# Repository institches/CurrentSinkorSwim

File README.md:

# CurrentSinkorSwim
Building a Current Sink for battery testing - Contextual Electronics

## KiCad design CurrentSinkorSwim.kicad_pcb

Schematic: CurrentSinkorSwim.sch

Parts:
J101, J103: Conn_01x02; Terminal_Block_200_thou
J102: Conn_01x03; Pin_Header_Straight_1x03_Pitch2.54mm

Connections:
/Current Control/Current_Sink+: J102.3, J103.1; also elsewhere on the board
/Power Regulation/Vin: J102.2; also elsewhere on the board
GND: J101.1, J103.2; also elsewhere on the board
unnamed: J101.2, J102.1

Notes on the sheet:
Battery Pack
Current Sink Input

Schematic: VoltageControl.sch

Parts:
C201: C; C_0805_HandSoldering
D201: D; D_SOD-523; MPN 1N4148WT-7
R201: 28.7K; R_0805
R202: 9K; R_0805
R203: 1K; R_0805
RV201: 10K; P090L-02F25BR10K
U201: LMV358; SOIC-8-N; MPN LMV358IDT

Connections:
2.7V: C201.1, R201.1, U201.8 (V+); also elsewhere on the board
/Current Control/Current_Sink+: R202.1; also elsewhere on the board
/Current Control/FET_Gate: D201.2; also elsewhere on the board
/Voltage Control/Current_Sink-: R203.2, RV201.3
GND: C201.2, U201.4 (V-); also elsewhere on the board
unnamed: D201.1, U201.1
unnamed: R201.2, RV201.2, U201.3 (+)
unnamed: R202.2, R203.1, U201.2 (-)

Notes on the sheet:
0-2V
0-20V

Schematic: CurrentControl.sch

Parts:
C301: C; C_0805_HandSoldering
J1: Conn_01x01; FA-T220-38E
Q301: BUK9575; TO-220-3_Vertical; MPN BUK9575-100A,127
R301: 68K; R_0805
R302: 1K; R_0805
R303: 0.1; R_Axial_DIN0516_L15.5mm_D5.0mm_P25.40mm_Horizontal; MPN AC01000001007JA100
RV301: 10K; P090L-02F25BR10K
U201: LMV358; SOIC-8-N

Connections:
2.7V: R301.1, U201.8 (V+); also elsewhere on the board
/Current Control/Current_Sink+: Q301.1 (D); also elsewhere on the board
/Current Control/FET_Gate: Q301.2 (G), R302.1; also elsewhere on the board
GND: C301.2, R303.2, RV301.2, U201.4 (V-); also elsewhere on the board
unnamed: Q301.3 (S), R303.1, U201.6 (-)
unnamed: R301.2, RV301.1, U201.5 (+)
unnamed: R302.2, U201.7

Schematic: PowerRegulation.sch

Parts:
C401, C402: C; C_0805_HandSoldering
R401: 27K; R_0805; MPN Value
R402: 21.6; R_0805
R403: 0; R_0805; MPN Value
U401: LM2931D-R; SOIC-8-N

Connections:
2.7V: C402.1, U401.8; also elsewhere on the board
/Power Regulation/Vin: C401.1, R401.1, U401.1; also elsewhere on the board
GND: C401.2, C402.2, R402.2, R403.2, U401.2, U401.3, U401.6, U401.7; also elsewhere on the board
unnamed: R401.2, R402.1, U401.4
unnamed: R403.1, U401.5

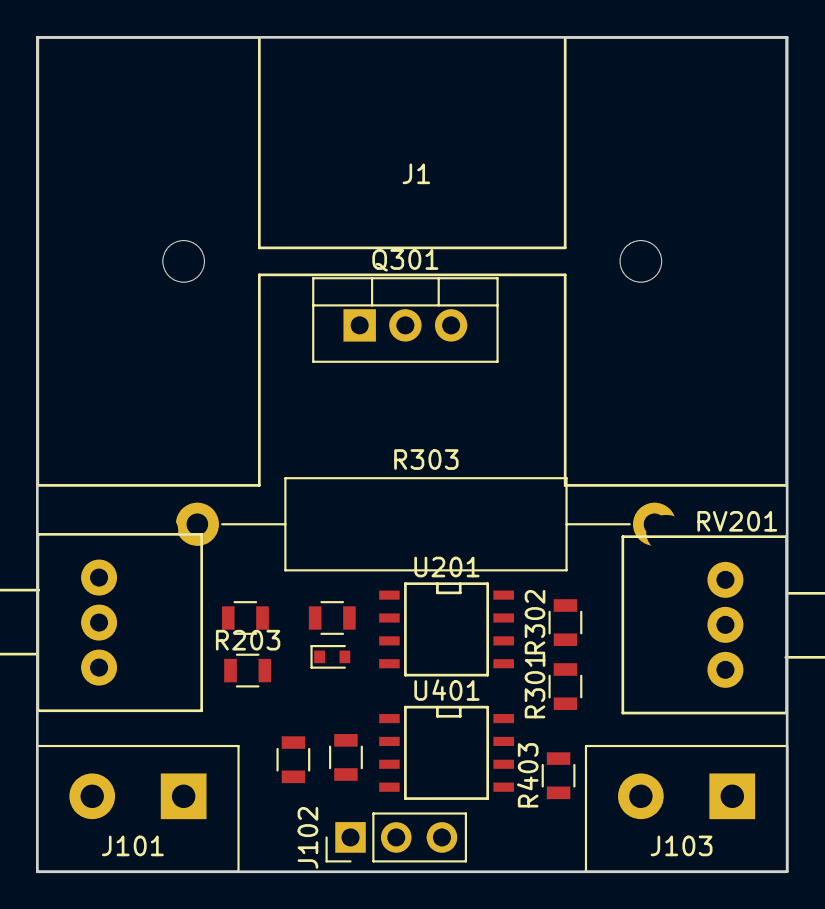
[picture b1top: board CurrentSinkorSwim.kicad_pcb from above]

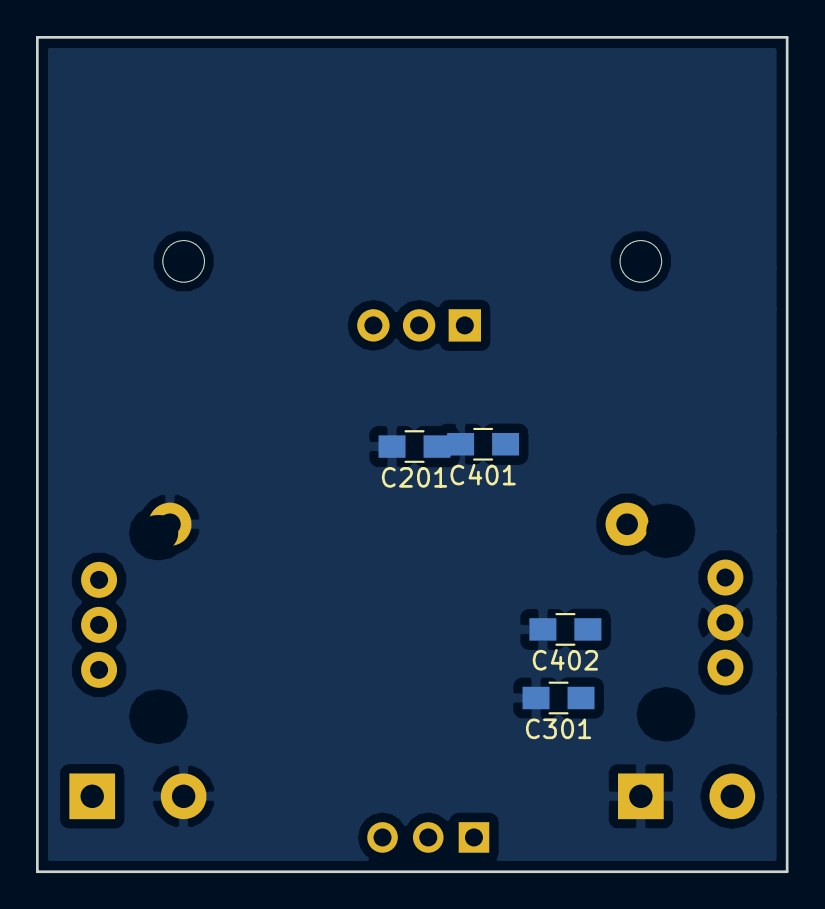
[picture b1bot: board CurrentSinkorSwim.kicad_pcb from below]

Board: 2 copper layers, 41.7 x 46.4 mm, 23 parts (4 on the bottom side), 15 nets, no tracks yet.

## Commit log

2018-06-09 KiCad files initial upload
2018-06-13 adding new sheets and voltage control circuit
2018-06-18 Initial Annotation
2018-06-18 Added footprints. Created initial netlist.
2018-06-27 Update connector footprints
2018-07-02 Fixed divider resistors and found valus. Added pot footprint.
2018-07-02 Moved components. Changed board outline. Added keepout area. Back side ground plane fill.
2018-07-09 Downloaded Chris' files after CSOS Layout session 1 and this is after Session 2.
    Moved pots/terms and routed traces to all components.
